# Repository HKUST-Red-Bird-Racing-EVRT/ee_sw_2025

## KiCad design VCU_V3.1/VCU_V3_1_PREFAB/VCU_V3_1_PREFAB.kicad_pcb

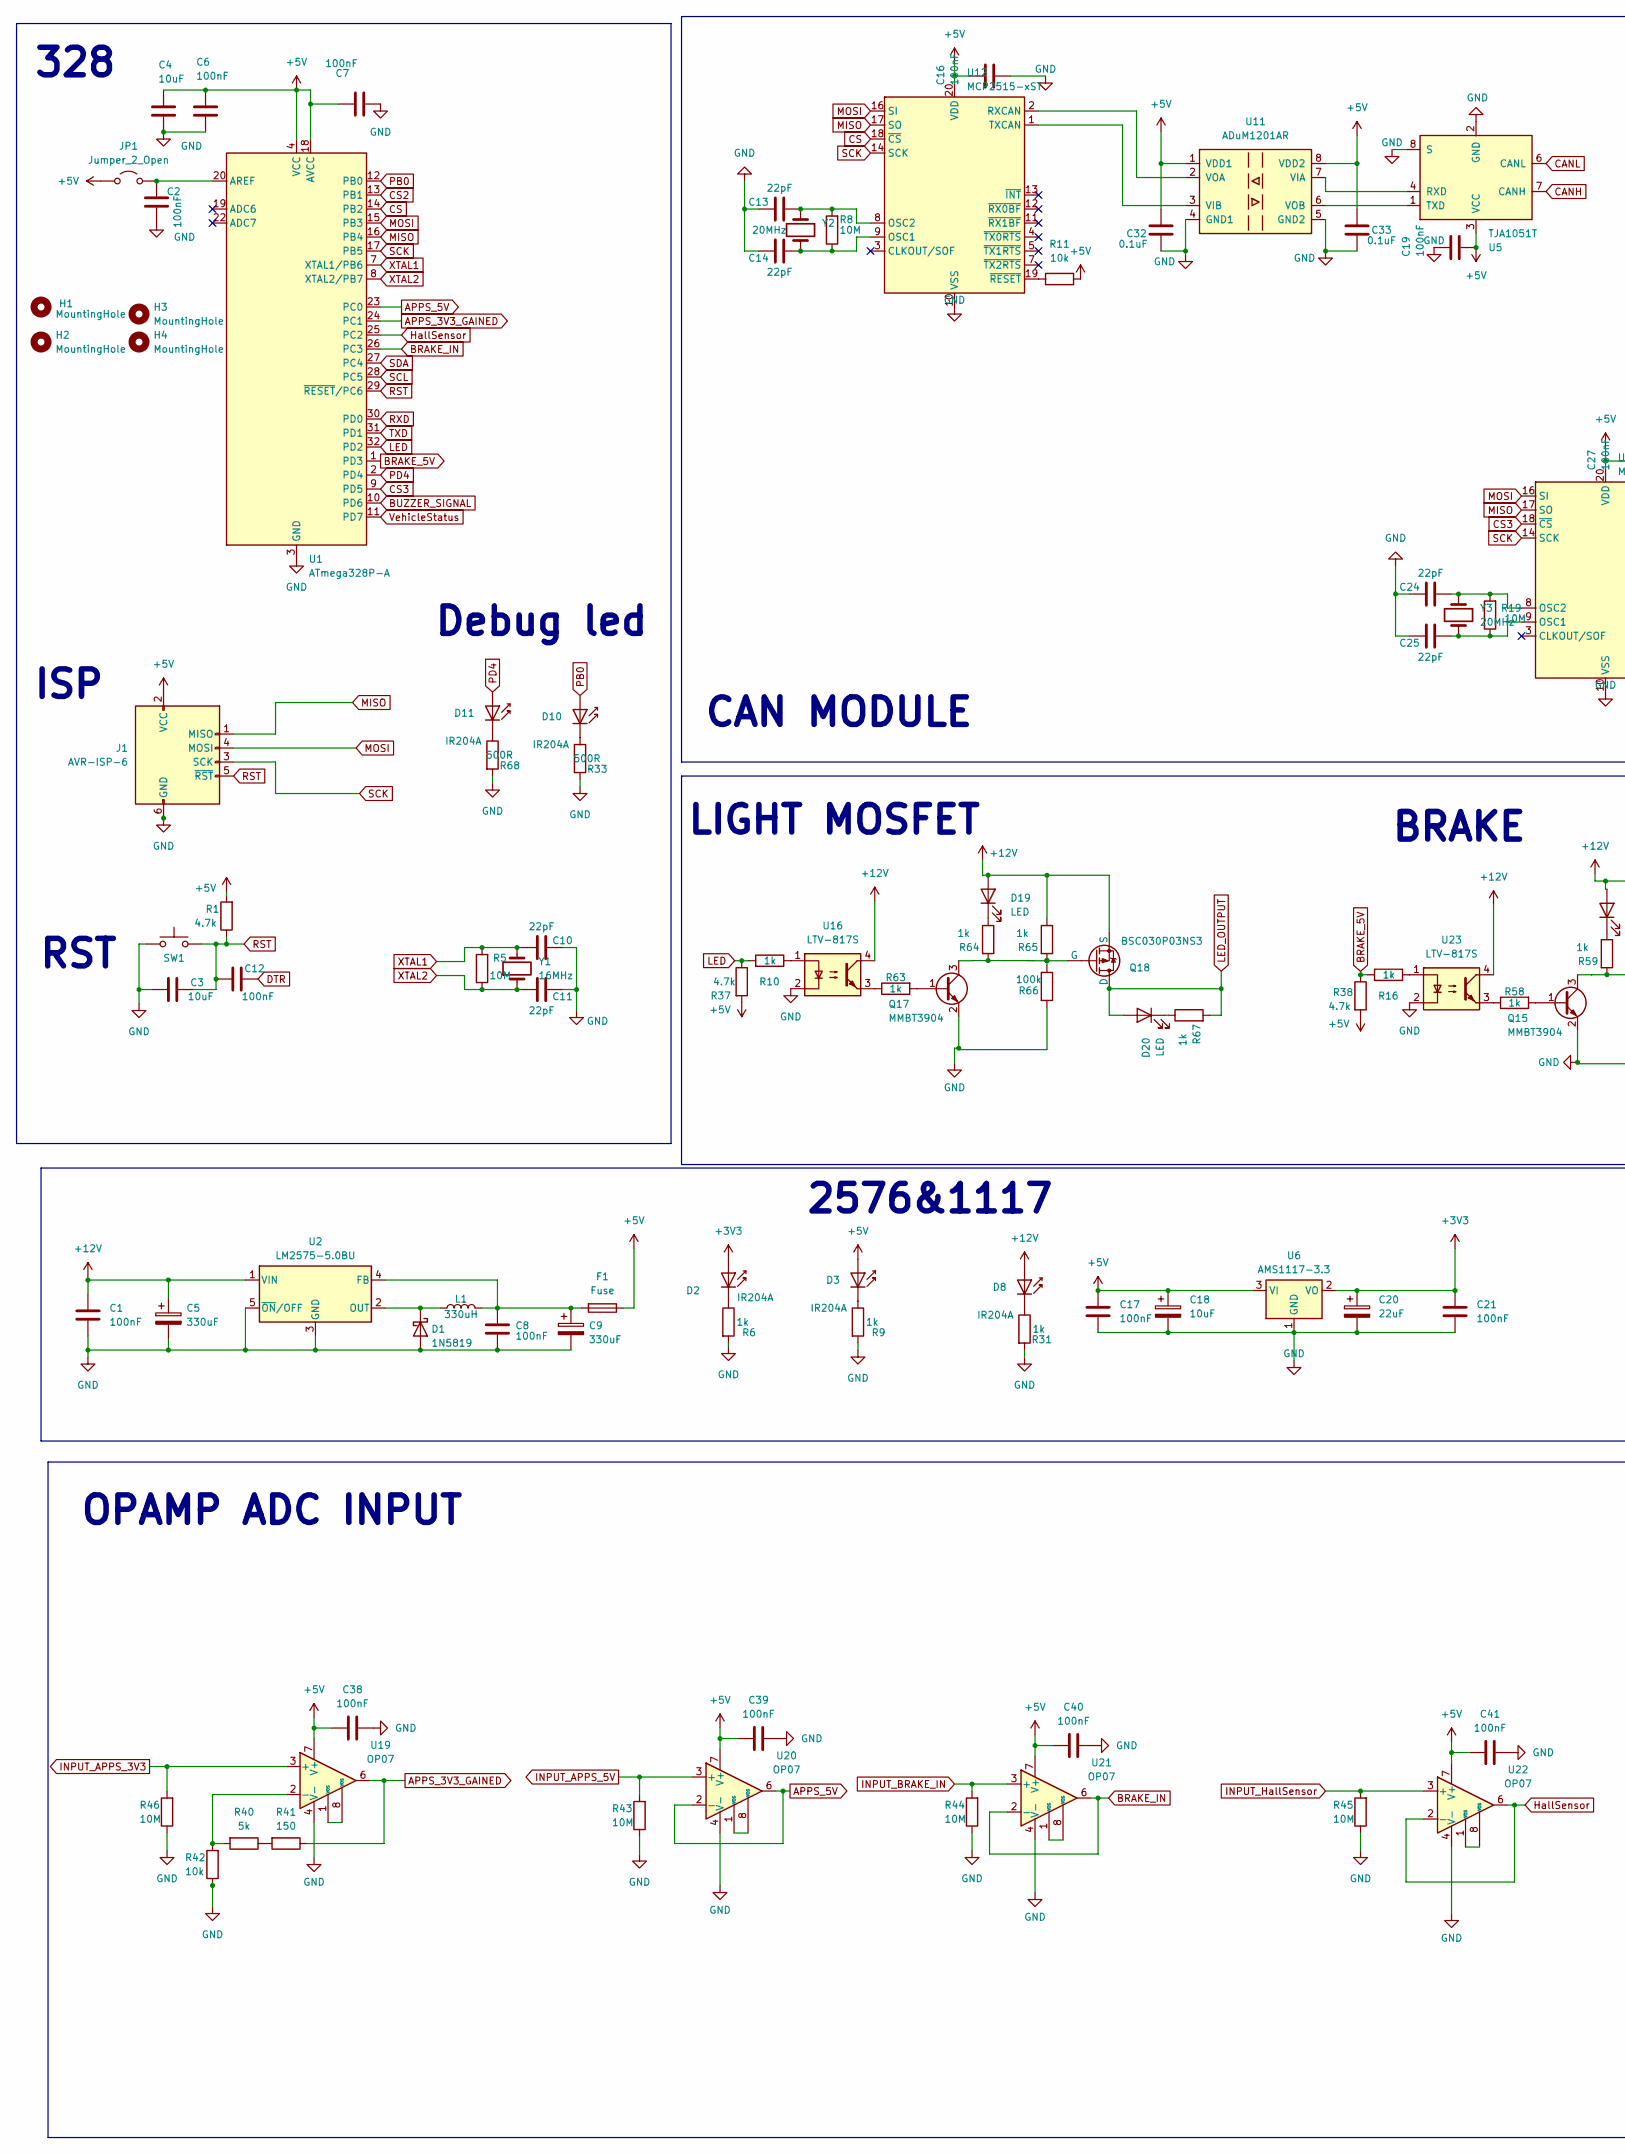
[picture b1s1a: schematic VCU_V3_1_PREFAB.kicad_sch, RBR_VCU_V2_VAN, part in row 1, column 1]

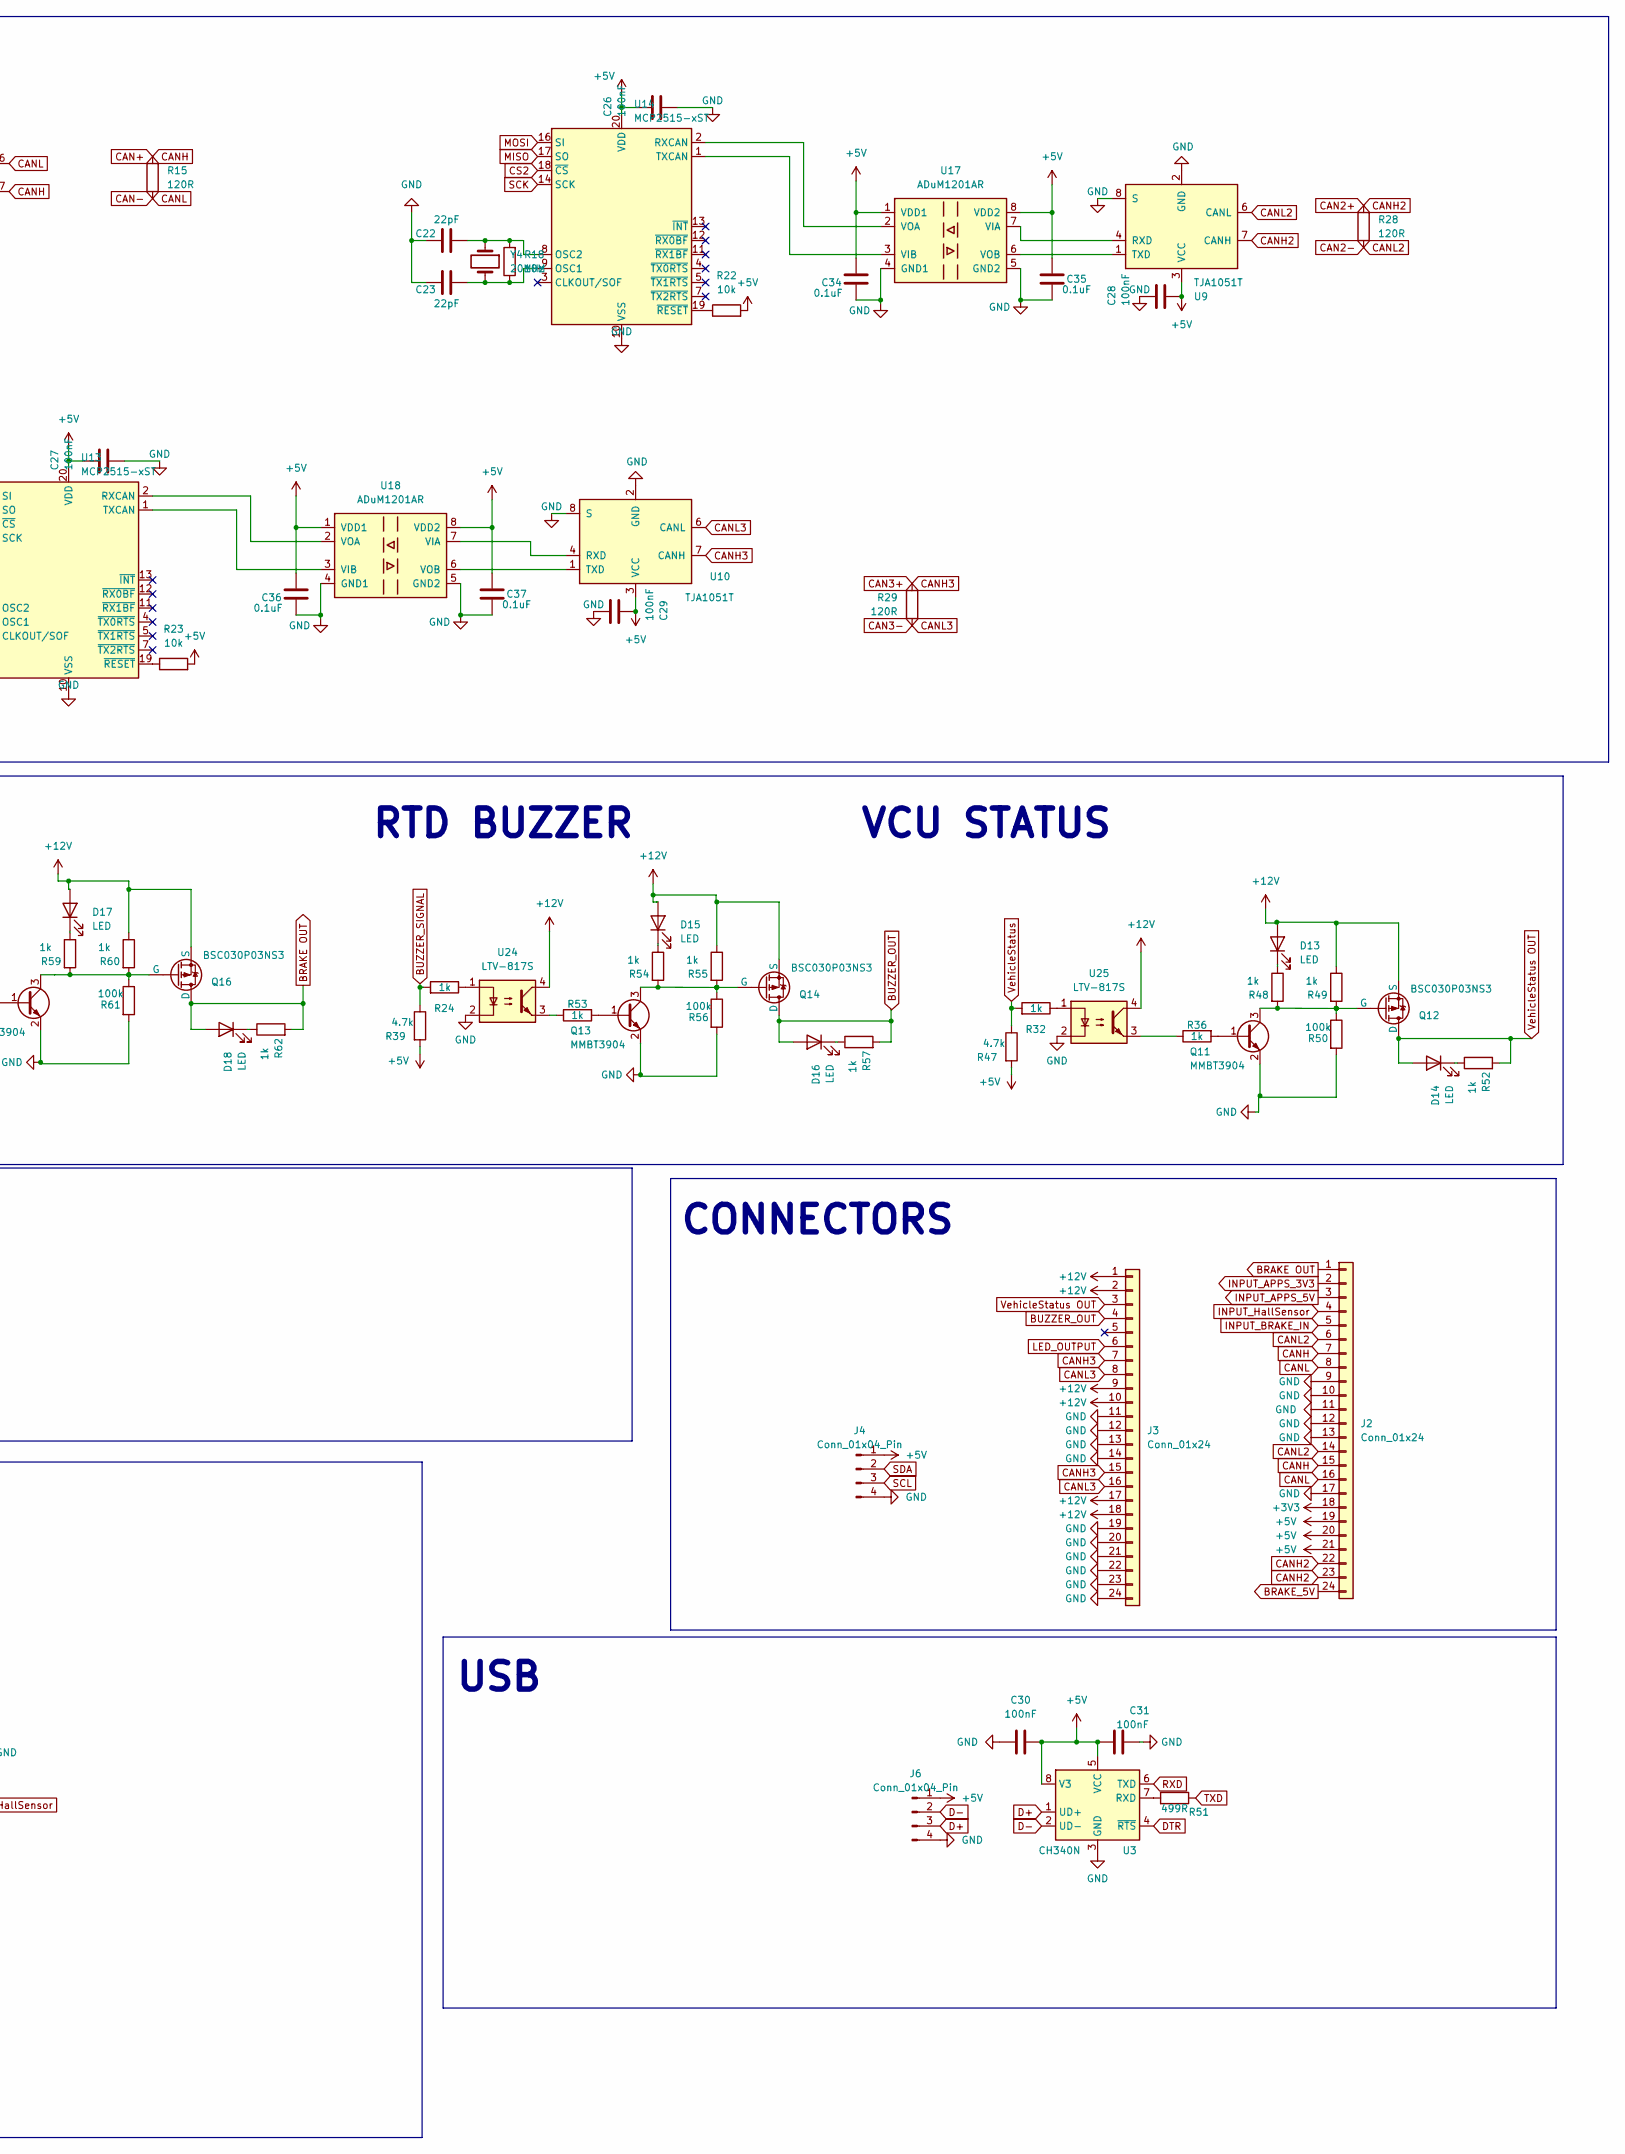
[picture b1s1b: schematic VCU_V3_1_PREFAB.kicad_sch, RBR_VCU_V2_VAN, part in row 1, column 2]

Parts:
C1, C2, C6, C7, C8, C12, C16, C17, C19, C21, C26, C27, C28, C29, C30, C31, C38, C39, C40, C41: 100nF; C_0805_2012Metric_Pad1.18x1.45mm_HandSolder_L
C3, C4, C18: 10uF; C_0805_2012Metric_Pad1.18x1.45mm_HandSolder_L
C5, C9: 330uF; CP_Radial_D10.0mm_P5.00mm_F
C10, C11, C13, C14, C22, C23, C24, C25: 22pF; C_0805_2012Metric_Pad1.18x1.45mm_HandSolder_L
C20: 22uF; C_0805_2012Metric_Pad1.18x1.45mm_HandSolder_L
C32, C33, C34, C35, C36, C37: 0.1uF; C_0805_2012Metric_Pad1.18x1.45mm_HandSolder_L
D1: 1N5819; D_SMA_Handsoldering
D2, D3, D8, D10, D11: IR204A; LED_1206_3216Metric_Pad1.42x1.75mm_HandSolder
D13, D14, D15, D16, D17, D18, D19, D20: LED; LED_0805_2012Metric_Pad1.45x1.40mm_HandSolder
F1: Fuse; Fuse_1210_3225Metric_Pad1.42x2.65mm_HandSolder
H1, H2, H3, H4: MountingHole; MountingHole_3.2mm_M3
J1: AVR-ISP-6; PinHeader_2x03_P2.54mm_Vertical
J2, J3: Conn_01x24; HD241_24pin
J4, J6: Conn_01x04_Pin; JST_XH_B4B-XH-A_1x04_P2.50mm_Vertical
JP1: Jumper_2_Open; SolderJumper-2_P1.3mm_Open_Pad1.0x1.5mm
L1: 330uH; L_TDK_SLF12575
Q11, Q13, Q15, Q17: MMBT3904; SOT-23
Q12, Q14, Q16, Q18: BSC030P03NS3; Infineon_PG-TDSON-8_6.15x5.15mm
R1, R37, R38, R39, R47: 4.7k; R_0805_2012Metric_Pad1.20x1.40mm_HandSolder_L
R5, R8, R18, R19, R43, R44, R45, R46: 10M; R_0805_2012Metric_Pad1.20x1.40mm_HandSolder_L
R6, R9, R10, R16, R24, R31, R32, R36, R48, R49, R52, R53, R54, R55, R57, R58, R59, R60, R62, R63, R64, R65, R67: 1k; R_0805_2012Metric_Pad1.20x1.40mm_HandSolder_L
R11, R22, R23, R42: 10k; R_0805_2012Metric_Pad1.20x1.40mm_HandSolder_L
R15, R28, R29: 120R; R_0805_2012Metric_Pad1.20x1.40mm_HandSolder_L
R33, R68: 500R; R_0805_2012Metric_Pad1.20x1.40mm_HandSolder_L
R40: 5k; R_0805_2012Metric_Pad1.20x1.40mm_HandSolder_L
R41: 150; R_0805_2012Metric_Pad1.20x1.40mm_HandSolder_L
R50, R56, R61, R66: 100k; R_0805_2012Metric_Pad1.20x1.40mm_HandSolder_L
R51: 499R; R_0805_2012Metric_Pad1.20x1.40mm_HandSolder_L
SW1: SW_Push; SW_PUSH_6mm_H5mm
U1: ATmega328P-A; TQFP-32_7x7mm_P0.8mm_L
U2: LM2575-5.0BU; TO-263-5_TabPin3
U3: CH340N; SOIC-8_3.9x4.9mm_P1.27mm_RMC_Handsolder
U5, U9, U10: TJA1051T; SOIC-8_3.9x4.9mm_P1.27mm_RMC_Handsolder
U6: AMS1117-3.3; SOT-223-3_TabPin2_Handsolder
U11, U17, U18: ADuM1201AR; SOIC-8_3.9x4.9mm_P1.27mm_RMC_Handsolder
U12, U13, U14: MCP2515-xST; TSSOP-20_4.4x6.5mm_P0.65mm
U16, U23, U24, U25: LTV-817S; SMDIP-4_W9.53mm
U19, U20, U21, U22: OP07; SOIC-8_3.9x4.9mm_P1.27mm_RMC_Handsolder
Y1: 16MHz; Crystal_HC49-U_Vertical_W_SMD
Y2, Y3, Y4: 20MHz; Crystal_HC49-U_Vertical_W_SMD

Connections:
+3V3: C20.1, C21.1, D2.2 (A), J2.18, U6.2 (VO)
+5V: C4.2, C6.2, C7.2, C16.2, C17.1, C18.1, C19.1, C26.2, C27.2, C28.1, C29.2, C30.2, C31.1, C32.2, C33.2, C34.2, C35.2, C36.2, C37.2, C38.1, C39.1, C40.1, C41.1, D3.2 (A), F1.1, J1.2 (VCC), J2.19, J2.20, J2.21, J4.1, J6.1, JP1.1 (A), R1.2, R11.2, R22.2, R23.2, R37.2, R38.2, R39.2, R47.2, U1.4 (VCC), U1.6 (VCC), U1.18 (AVCC), U3.5 (VCC), U3.8 (V3), U5.3 (VCC), U6.3 (VI), U9.3 (VCC), U10.3 (VCC), U11.1 (VDD1), U11.8 (VDD2), U12.20 (VDD), U13.20 (VDD), U14.20 (VDD), U17.1 (VDD1), U17.8 (VDD2), U18.1 (VDD1), U18.8 (VDD2), U19.7 (V+), U20.7 (V+), U21.7 (V+), U22.7 (V+)
+12V: C1.1, C5.1, D8.2 (A), D13.2 (A), D15.2 (A), D17.2 (A), D19.2 (A), J3.1, J3.2, J3.9, J3.10, J3.17, J3.18, Q12.1 (S), Q12.2 (S), Q12.3 (S), Q14.1 (S), Q14.2 (S), Q14.3 (S), Q16.1 (S), Q16.2 (S), Q16.3 (S), Q18.1 (S), Q18.2 (S), Q18.3 (S), R49.1, R55.1, R60.1, R65.1, U2.1 (VIN), U16.4, U23.4, U24.4, U25.4
APPS_3V3_GAINED: R41.1, U1.24 (PC1), U19.6
APPS_5V: U1.23 (PC0), U20.2 (-), U20.6
BRAKE OUT: D18.2 (A), J2.1, Q16.5 (D), Q16.6 (D), Q16.7 (D), Q16.8 (D), R62.2
BRAKE_5V: J2.24, R16.2, R38.1, U1.1 (PD3)
BRAKE_IN: U1.26 (PC3), U21.2 (-), U21.6
BUZZER_OUT: D16.2 (A), J3.4, Q14.5 (D), Q14.6 (D), Q14.7 (D), Q14.8 (D), R57.2
BUZZER_SIGNAL: R24.2, R39.1, U1.10 (PD6)
CAN2+: J2.22, J2.23, R28.2, U9.7 (CANH)
CAN2-: J2.6, J2.14, R28.1, U9.6 (CANL)
CAN3+: J3.7, J3.15, R29.2, U10.7 (CANH)
CAN3-: J3.8, J3.16, R29.1, U10.6 (CANL)
CAN+: J2.7, J2.15, R15.2, U5.7 (CANH)
CAN-: J2.8, J2.16, R15.1, U5.6 (CANL)
CS: U1.14 (PB2), U12.18 (~CS)
CS2: U1.13 (PB1), U14.18 (~CS)
CS3: U1.9 (PD5), U13.18 (~CS)
D+: J6.3, U3.1 (UD+)
D-: J6.2, U3.2 (UD-)
DTR: C12.2, U3.4 (~RTS)
GND: C1.2, C2.2, C3.1, C4.1, C5.2, C6.1, C7.1, C8.2, C9.2, C10.1, C11.1, C13.1, C14.1, C16.1, C17.2, C18.2, C19.2, C20.2, C21.2, C22.1, C23.1, C24.1, C25.1, C26.1, C27.1, C28.2, C29.1, C30.1, C31.2, C32.1, C33.1, C34.1, C35.1, C36.1, C37.1, C38.2, C39.2, C40.2, C41.2, D1.2 (A), J1.6 (GND), J2.9, J2.10, J2.11, J2.12, J2.13, J2.17, J3.11, J3.12, J3.13, J3.14, J3.19, J3.20, J3.21, J3.22, J3.23, J3.24, J4.4, J6.4, Q11.2 (E), Q13.2 (E), Q15.2 (E), Q17.2 (E), R6.2, R9.2, R31.2, R33.2, R42.1, R43.1, R44.1, R45.1, R46.1, R50.2, R56.2, R61.2, R66.2, R68.2, SW1.1, U1.3 (GND), U1.5 (GND), U1.21 (GND), U2.3 (GND), U2.5 (~ON/OFF), U3.3 (GND), U5.2 (GND), U5.8 (S), U6.1 (GND), U9.2 (GND), U9.8 (S), U10.2 (GND), U10.8 (S), U11.4 (GND1), U11.5 (GND2), U12.10 (VSS), U13.10 (VSS), U14.10 (VSS), U16.2, U17.4 (GND1), U17.5 (GND2), U18.4 (GND1), U18.5 (GND2), U19.4 (V-), U20.4 (V-), U21.4 (V-), U22.4 (V-), U23.2, U24.2, U25.2
HallSensor: U1.25 (PC2), U22.2 (-), U22.6
INPUT_APPS_3V3: J2.2, R46.2, U19.3 (+)
INPUT_APPS_5V: J2.3, R43.2, U20.3 (+)
INPUT_BRAKE_IN: J2.5, R44.2, U21.3 (+)
INPUT_HallSensor: J2.4, R45.2, U22.3 (+)
LED: R10.2, R37.1, U1.32 (PD2)
LED_OUTPUT: D20.2 (A), J3.6, Q18.5 (D), Q18.6 (D), Q18.7 (D), Q18.8 (D), R67.2
MISO: J1.1 (MISO), U1.16 (PB4), U12.17 (SO), U13.17 (SO), U14.17 (SO)
MOSI: J1.4 (MOSI), U1.15 (PB3), U12.16 (SI), U13.16 (SI), U14.16 (SI)
unnamed: D1.1 (K), L1.1, U2.2 (OUT)
unnamed: D2.1 (K), R6.1
unnamed: D3.1 (K), R9.1
unnamed: D8.1 (K), R31.1
unnamed: D10.1 (K), R33.1
unnamed: D11.1 (K), R68.1
unnamed: D13.1 (K), R48.1
unnamed: D14.1 (K), R52.1
unnamed: D15.1 (K), R54.1
unnamed: D16.1 (K), R57.1
unnamed: D17.1 (K), R59.1
unnamed: D18.1 (K), R62.1
unnamed: D19.1 (K), R64.1
unnamed: D20.1 (K), R67.1
unnamed: C2.1, JP1.2 (B), U1.20 (AREF)
unnamed: Q11.1 (B), R36.2
unnamed: Q11.3 (C), Q12.4 (G), R48.2, R49.2, R50.1
unnamed: Q13.1 (B), R53.2
unnamed: Q13.3 (C), Q14.4 (G), R54.2, R55.2, R56.1
unnamed: Q15.1 (B), R58.2
unnamed: Q15.3 (C), Q16.4 (G), R59.2, R60.2, R61.1
unnamed: Q17.1 (B), R63.2
unnamed: Q17.3 (C), Q18.4 (G), R64.2, R65.2, R66.1
unnamed: R10.1, U16.1
unnamed: R16.1, U23.1
unnamed: R24.1, U24.1
unnamed: R32.1, U25.1
unnamed: R36.1, U25.3
unnamed: R40.1, R41.2
unnamed: R53.1, U24.3
unnamed: R58.1, U23.3
unnamed: R63.1, U16.3
unnamed: C8.1, C9.1, F1.2, L1.2, U2.4 (FB)
unnamed: R51.2, U3.7 (RXD)
unnamed: U10.4 (RXD), U18.7 (VIA)
unnamed: U10.1 (TXD), U18.6 (VOB)
unnamed: U5.4 (RXD), U11.7 (VIA)
unnamed: U11.3 (VIB), U12.1 (TXCAN)
unnamed: U11.2 (VOA), U12.2 (RXCAN)
unnamed: U5.1 (TXD), U11.6 (VOB)
unnamed: C14.2, R8.1, U12.9 (OSC1), Y2.2
unnamed: C13.2, R8.2, U12.8 (OSC2), Y2.1
unnamed: R11.1, U12.19 (~RESET)
unnamed: C25.2, R19.1, U13.9 (OSC1), Y3.2
unnamed: C24.2, R19.2, U13.8 (OSC2), Y3.1
unnamed: U13.2 (RXCAN), U18.2 (VOA)
unnamed: U13.1 (TXCAN), U18.3 (VIB)
unnamed: R23.1, U13.19 (~RESET)
unnamed: C23.2, R18.1, U14.9 (OSC1), Y4.2
unnamed: C22.2, R18.2, U14.8 (OSC2), Y4.1
unnamed: U14.2 (RXCAN), U17.2 (VOA)
unnamed: U14.1 (TXCAN), U17.3 (VIB)
unnamed: R22.1, U14.19 (~RESET)
unnamed: U9.4 (RXD), U17.7 (VIA)
unnamed: U9.1 (TXD), U17.6 (VOB)
unnamed: R40.2, R42.2, U19.2 (-)
unnamed: U19.1 (VOS), U19.8 (VOS)
unnamed: U20.1 (VOS), U20.8 (VOS)
unnamed: U21.1 (VOS), U21.8 (VOS)
unnamed: U22.1 (VOS), U22.8 (VOS)
PB0: D10.2 (A), U1.12 (PB0)
PD4: D11.2 (A), U1.2 (PD4)
RST: C3.2, C12.1, J1.5 (~RST), R1.1, SW1.2, U1.29 (~RESET/PC6)
RXD: U1.30 (PD0), U3.6 (TXD)
SCK: J1.3 (SCK), U1.17 (PB5), U12.14 (SCK), U13.14 (SCK), U14.14 (SCK)
SCL: J4.3, U1.28 (PC5)
SDA: J4.2, U1.27 (PC4)
TXD: R51.1, U1.31 (PD1)
VehicleStatus: R32.2, R47.1, U1.11 (PD7)
VehicleStatus OUT: D14.2 (A), J3.3, Q12.5 (D), Q12.6 (D), Q12.7 (D), Q12.8 (D), R52.2
XTAL1: C10.2, R5.2, U1.7 (XTAL1/PB6), Y1.2
XTAL2: C11.2, R5.1, U1.8 (XTAL2/PB7), Y1.1

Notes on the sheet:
RST
CONNECTORS
OPAMP ADC INPUT
RTD BUZZER
ISP
Debug led
2576&1117
VCU STATUS
LIGHT MOSFET
CAN MODULE
USB
BRAKE
328

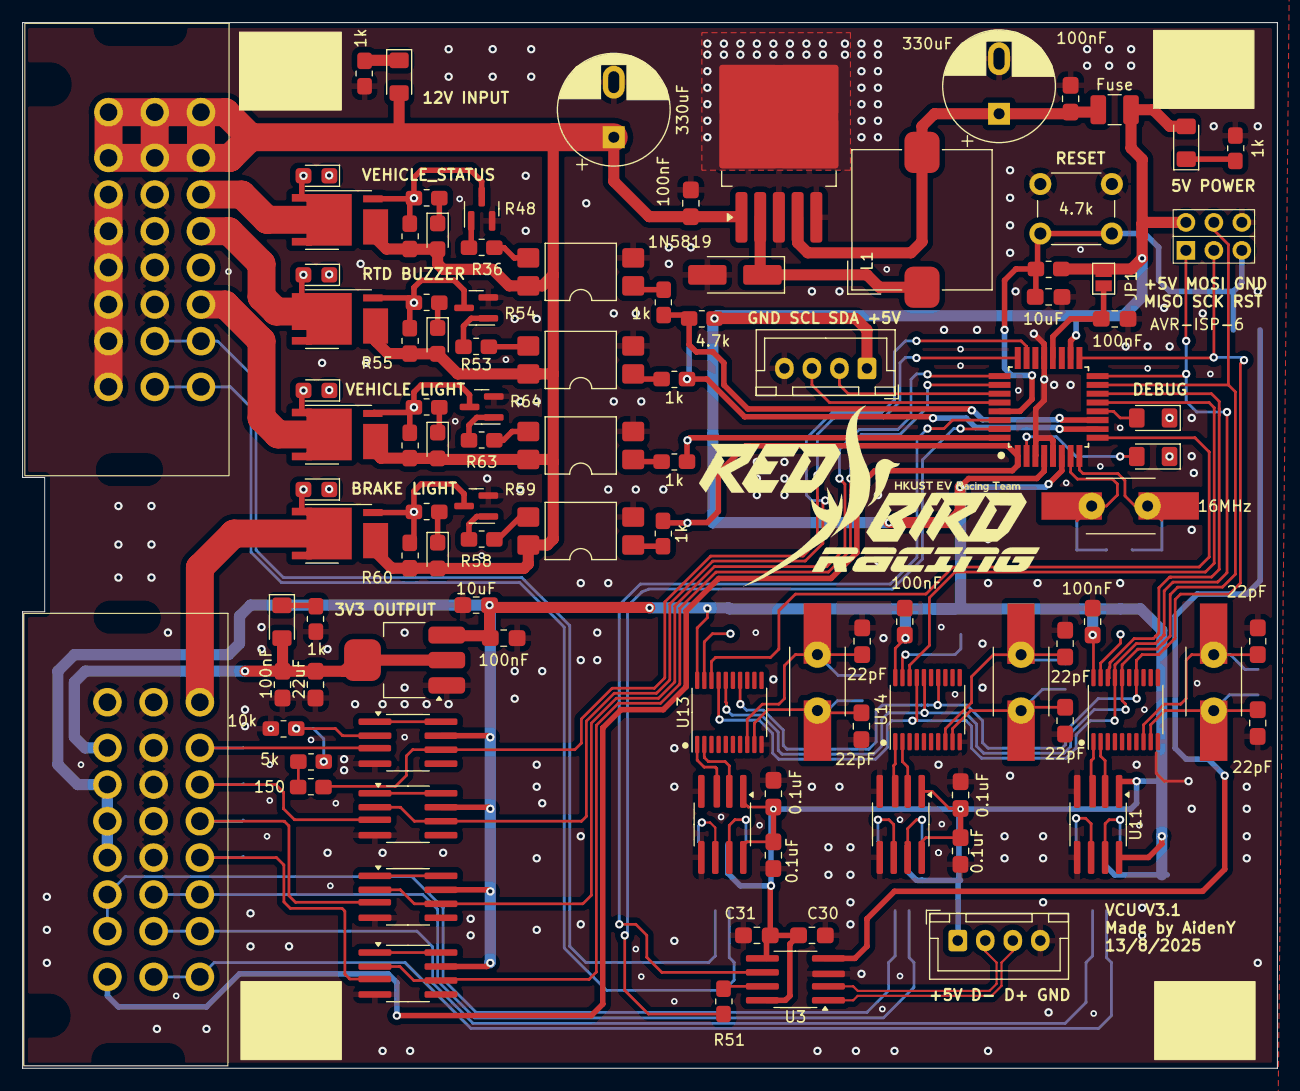
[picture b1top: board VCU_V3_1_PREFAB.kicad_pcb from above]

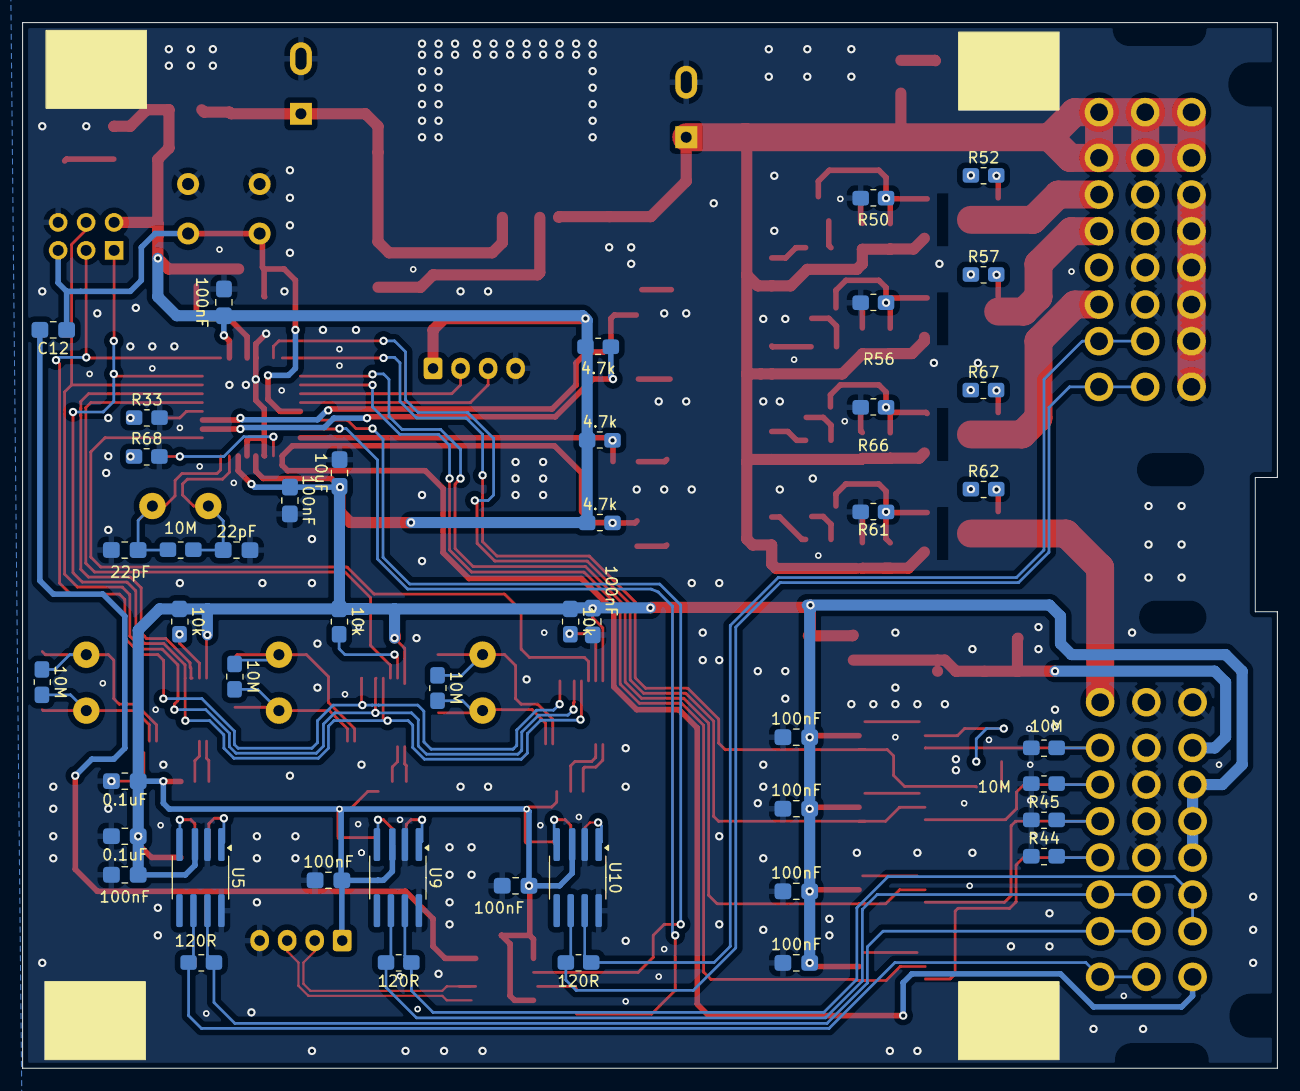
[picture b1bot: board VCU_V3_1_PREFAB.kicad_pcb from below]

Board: 2 copper layers, 114.0 x 95.0 mm, 152 parts (46 on the bottom side), 104 nets.
